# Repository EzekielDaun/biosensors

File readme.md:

# Biosensor

TODO: Description of the project itself.

## How to use Git

Before starting, be familiar with the [command line and shell](https://missing.csail.mit.edu/2020/course-shell/). (At least the `cd` command)

[Download and Installation Guide](https://git-scm.com/downloads)

### Resources

[Documentation](https://git-scm.com/doc)

[Cheat Sheet](https://training.github.com/downloads/github-git-cheat-sheet)

[Learn Git Branching](https://learngitbranching.js.org) (~1h) is an alternative to learning git branching interactively, and also a sandbox to play with.

### User

If you only want to use this repo but not change it:

- Clone the repository

  If you don't need any version-control feature from git, `Download ZIP` and you can omit the remaining sections of this readme.

  **Recommended:** `cd` to a place for the code (the `git clone` command will create a folder named `biosensors` under the working directory)

  ```git
  git clone https://github.com/SiEPIC/biosensors.git
  ```

- Get the latest update

  This will reset your local version to the remote version:

  ```git
  git reset --hard origin
  ```

- Switch to commit

  1. List commits

  ```git
  git log

      commit b4363207acb8847089aef8f59283cc06b60350ea (HEAD -> main, origin/main, origin/HEAD)
      Author: EzekielDaun <liuyifei0905@gmail.com>
      Date:   Fri Aug 26 16:57:51 2022 -0700

          📖 update RA-GUI readme

      commit 6c2b0750e4bcb03764c195b85f4f5f3b98b2843e
      Author: EzekielDaun <liuyifei0905@gmail.com>
      Date: Fri Aug 26 14:22:33 2022 -0700

          📖 add usage guide for pyOptomip

      commit a774aea0a90b7bd50cc8b93aa6908ee873252529
      Merge: e32ba9e 12f7248
      Author: Yifei Liu <34564223+EzekielDaun@users.noreply.github.com>
  ```

  2. No need to type the full commit hash

  ```git
  git reset b436320
  ```

- Switch to branch
  ```git
  git checkout my_branch
  ```

### Developer

It's highly recommended for developers to be familiar with all topics in [Git Branching](https://learngitbranching.js.org), especially the `remote` section.

A typical git workflow is like [this](https://git-scm.com/about/branching-and-merging) or as follows:

```mermaid
    gitGraph
       commit
       branch develop
       checkout develop
       commit
       checkout main
       merge develop
       checkout develop
       branch topic
       commit
       checkout develop
       commit
       merge topic
       commit
       checkout main
       merge develop
```

A more advanced version for large projects:[^1]

[^1]: At the time of this figure, the default branch naming convention is "master". Now, "main" is preferred. [More](https://github.com/github/renaming)

For our project (a few developers with less frequent commits), a single main branch with feature/hotfix branches is enough.

A proposed workflow is:

1. check out a new branch from `main` with a proper name
2. commit your changes and push that branch to remote
3. create a Pull Request (PR) to merge your changes into `main` and request other members to review
4. update, commit and push your following modifications to that PR branch
5. merge into the main branch
6. delete feature/hotfix branch.

```mermaid
    gitGraph
      checkout main
      commit
      branch feature1
      checkout feature1
      commit
      checkout main
      branch feature2
      checkout feature2
      commit
      checkout main
      merge feature1
      merge feature2
```

[GitHub-Flow](https://docs.github.com/en/get-started/quickstart/github-flow)

#### Merge Conflicts

When multiple members work on the same project, merge conflicts can be tricky. As of this writing, there has never been such a situation yet.

A few tips just in case it happens:

- When resolving merge conflicts, make sure to select the correct changes. Test the functionality after merge.
- Force push (`git push --force`) if you believe an overwrite is easier. And **BE CAREFUL**.
- Pull from origin frequently with the rebase option (`git pull --rebase`) to avoid/reveal potential conflicts in advance.

[More about force push and rebase](https://docs.gitlab.com/ee/topics/git/git_rebase.html)

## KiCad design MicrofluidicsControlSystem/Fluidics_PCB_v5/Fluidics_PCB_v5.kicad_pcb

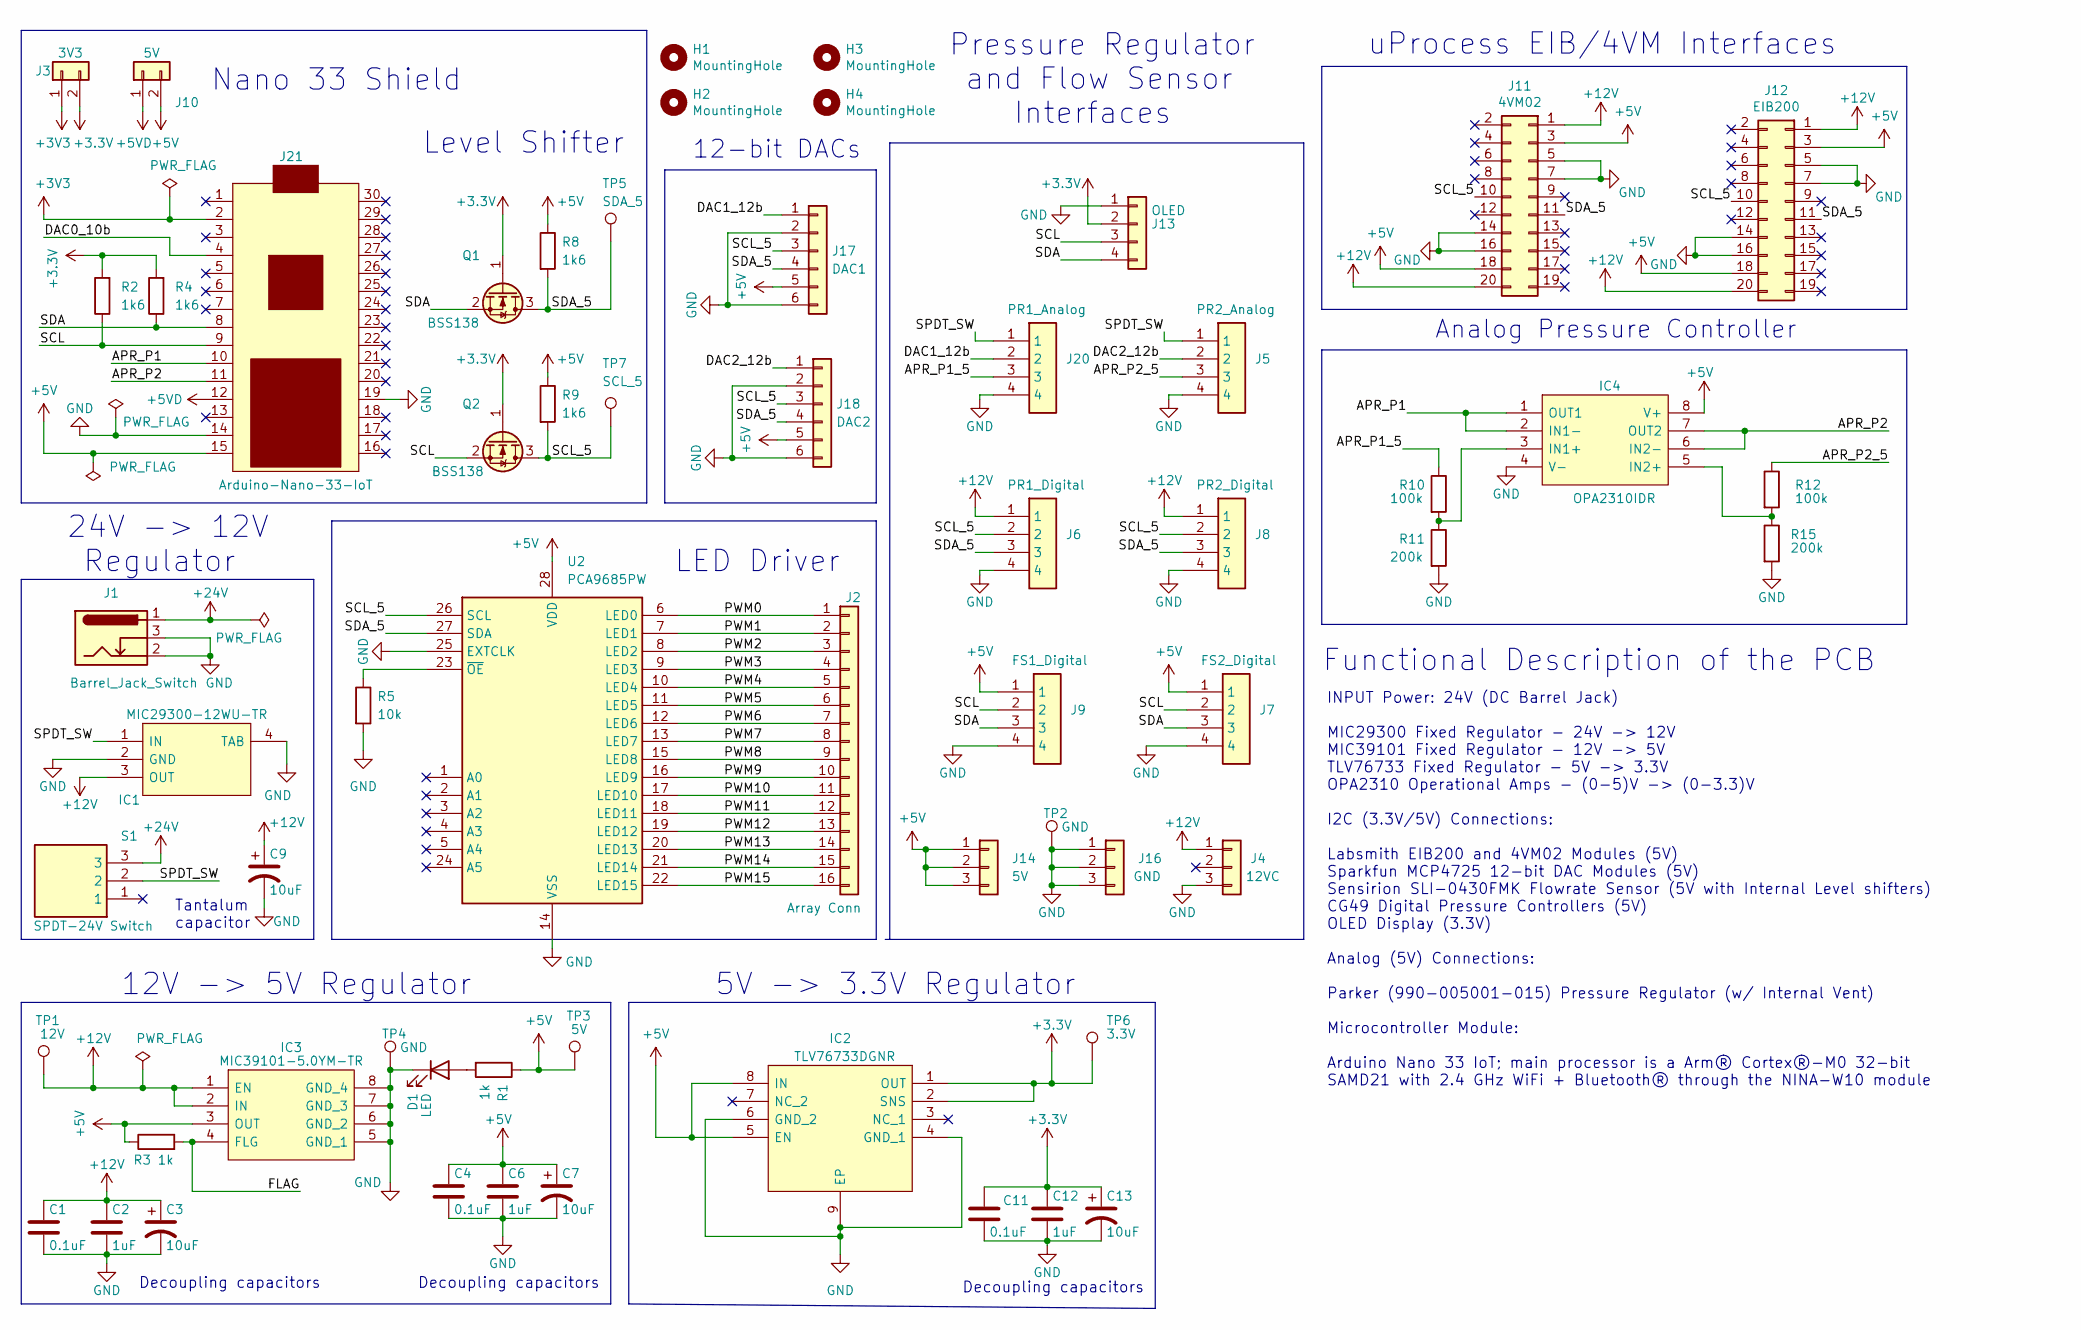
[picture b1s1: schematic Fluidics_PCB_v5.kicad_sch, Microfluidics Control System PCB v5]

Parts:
C1, C4, C11: 0.1uF; C_0603_1608Metric
C2, C6, C12: 1uF; C_0603_1608Metric
C3, C7, C13: 10uF; C_0805_2012Metric
C9: 10uF; CP_EIA-3528-12_Kemet-T
D1: LED; LED_0805_2012Metric
H1, H2, H3, H4: MountingHole; MountingHole_3.2mm_M3
IC1: MIC29300-12WU-TR; MIC2930012WUTR; Mouser Part Number 998-MIC29300-12WUTR
IC2: TLV76733DGNR; SOP65P490X110-9N; Manufacturer_Part_Number TLV76733DGNR; Mouser Part Number 595-TLV76733DGNR
IC3: MIC39101-5.0YM-TR; SOIC127P599X173-8N; Manufacturer_Part_Number MIC39101-5.0YM-TR; Mouser Part Number 998-MIC39101-5.0YMTR
IC4: OPA2310IDR; SOIC127P600X175-8N; Mouser Part Number 595-OPA2310IDR
J1: Barrel_Jack_Switch; BarrelJack_CLIFF_FC681465S_SMT_Horizontal
J2: Array Conn; PinSocket_2x08_P2.54mm_Vertical_SMD
J3: 3V3; PinHeader_1x02_P2.54mm_Vertical
J4: 12VC; PinSocket_1x03_P2.54mm_Vertical
J5: PR2_Analog; 110990030; Mouser Part Number 713-110990030
J6: PR1_Digital; 110990030; Mouser Part Number 713-110990030
J7: FS2_Digital; 110990030; Mouser Part Number 713-110990030
J8: PR2_Digital; 110990030; Mouser Part Number 713-110990030
J9: FS1_Digital; 110990030; Mouser Part Number 713-110990030
J10: 5V; PinHeader_1x02_P2.54mm_Vertical
J11: 4VM02
J12: EIB200
J13: OLED; PinSocket_1x04_P2.54mm_Vertical
J14: 5V; PinSocket_1x03_P2.54mm_Vertical
J16: GND; PinSocket_1x03_P2.54mm_Vertical
J17: DAC1; PinSocket_1x06_P2.54mm_Vertical
J18: DAC2; PinSocket_1x06_P2.54mm_Vertical
J20: PR1_Analog; 110990030; Mouser Part Number 713-110990030
J21: Arduino-Nano-33-IoT; NANO_33_Footprint_SMD_Castell
Q1, Q2: BSS138; SOT-23
R1, R3: 1k; R_0603_1608Metric
R2, R4, R8, R9: 1k6; R_0603_1608Metric
R5: 10k; R_0603_1608Metric
R10, R12: 100k; R_0603_1608Metric
R11, R15: 200k; R_0603_1608Metric
S1: SPDT-24V Switch; 8SS1012Z; Manufacturer_Part_Number 8SS1012-Z
TP1: 12V; TestPoint_THTPad_D2.0mm_Drill1.0mm
TP2, TP4: GND; TestPoint_THTPad_D2.0mm_Drill1.0mm
TP3: 5V; TestPoint_THTPad_D2.0mm_Drill1.0mm
TP5: SDA_5; TestPoint_THTPad_D2.0mm_Drill1.0mm
TP6: 3.3V; TestPoint_THTPad_D2.0mm_Drill1.0mm
TP7: SCL_5; TestPoint_THTPad_D2.0mm_Drill1.0mm
U2: PCA9685PW; TSSOP-28_4.4x9.7mm_P0.65mm

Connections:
+3.3V: C11.1, C12.1, C13.1, IC2.1 (OUT), IC2.2 (SNS), J3.2, J13.2, Q1.1 (G), Q2.1 (G), R2.2, R4.2, TP6.1
+3V3: J3.1, J21.2
+5V: C4.1, C6.1, C7.1, IC2.5 (EN), IC2.8 (IN), IC3.3 (OUT), IC4.8 (V+), J7.1, J9.1, J10.2, J11.3, J11.18, J12.3, J12.18, J14.1, J14.2, J14.3, J17.5, J18.5, J21.15, R1.1, R3.1, R8.1, R9.1, TP3.1, U2.28 (VDD)
+5VD: J10.1, J21.12
+12V: C1.1, C2.1, C3.1, C9.1, IC1.3 (OUT), IC3.1 (EN), IC3.2 (IN), J4.1, J6.1, J8.1, J11.1, J11.20, J12.1, J12.20, TP1.1
+24V: J1.1, S1.3
/APR_P1: IC4.1 (OUT1), IC4.2 (IN1-), J21.10
/APR_P1_5: J20.3, R10.1
/APR_P2: IC4.6 (IN2-), IC4.7 (OUT2), J21.11
/APR_P2_5: J5.3, R12.1
/DAC0_10b: J21.4
/DAC1_12b: J17.1, J20.2
/DAC2_12b: J5.2, J18.1
/FLAG: IC3.4 (FLG), R3.2
/PWM0: J2.1, U2.6 (LED0)
/PWM1: J2.2, U2.7 (LED1)
/PWM2: J2.3, U2.8 (LED2)
/PWM3: J2.4, U2.9 (LED3)
/PWM4: J2.5, U2.10 (LED4)
/PWM5: J2.6, U2.11 (LED5)
/PWM6: J2.7, U2.12 (LED6)
/PWM7: J2.8, U2.13 (LED7)
/PWM8: J2.9, U2.15 (LED8)
/PWM9: J2.10, U2.16 (LED9)
/PWM10: J2.11, U2.17 (LED10)
/PWM11: J2.12, U2.18 (LED11)
/PWM12: J2.13, U2.19 (LED12)
/PWM13: J2.14, U2.20 (LED13)
/PWM14: J2.15, U2.21 (LED14)
/PWM15: J2.16, U2.22 (LED15)
/SCL: J7.2, J9.2, J13.3, J21.9, Q2.2 (S), R2.1
/SCL_5: J6.2, J8.2, J11.10, J12.10, J17.3, J18.3, Q2.3 (D), R9.2, TP7.1, U2.26 (SCL)
/SDA: J7.3, J9.3, J13.4, J21.8, Q1.2 (S), R4.1
/SDA_5: J6.3, J8.3, J11.11, J12.11, J17.4, J18.4, Q1.3 (D), R8.2, TP5.1, U2.27 (SDA)
/SPDT_SW: IC1.1 (IN), J5.1, J20.1, S1.2
GND: C1.2, C2.2, C3.2, C4.2, C6.2, C7.2, C9.2, C11.2, C12.2, C13.2, D1.1 (K), IC1.2 (GND), IC1.4 (TAB), IC2.4 (GND_1), IC2.6 (GND_2), IC2.9 (EP), IC3.5 (GND_1), IC3.6 (GND_2), IC3.7 (GND_3), IC3.8 (GND_4), IC4.4 (V-), J1.2, J1.3, J4.3, J5.4, J6.4, J7.4, J8.4, J9.4, J11.5, J11.7, J11.14, J11.16, J12.5, J12.7, J12.14, J12.16, J13.1, J16.1, J16.2, J16.3, J17.2, J17.6, J18.2, J18.6, J20.4, J21.14, J21.19, R5.2, R11.2, R15.2, TP2.1, TP4.1, U2.14 (VSS), U2.25 (EXTCLK); also elsewhere on the board
unnamed: D1.2 (A), R1.2
unnamed: IC4.3 (IN1+), R10.2, R11.1
unnamed: IC4.5 (IN2+), R12.2, R15.1
unnamed: R5.1, U2.23 (~OE)

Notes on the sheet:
Pressure Regulator and Flow Sensor Interfaces
INPUT Power: 24V (DC Barrel Jack) MIC29300 Fixed Regulator - 24V -> 12V MIC39101 Fixed Regulator - 12V -> 5V TLV76733 Fixed Regulator - 5V -> 3.3V OPA2310 Operational Amps - (0-5)V -> (0-3.3)V I2C (3.3V/5V) Connections: Labsmith EIB200 and 4VM02 Modules (5V) Sparkfun MCP4725 12-bit DAC Modules (5V)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
uProcess EIB/4VM Interfaces
Decoupling capacitors
24V -> 12V Regulator
Analog Pressure Controller
Functional Description of the PCB
Tantalum capacitor
Level Shifter
Nano 33 Shield
12-bit DACs
5V -> 3.3V Regulator
LED Driver
12V -> 5V Regulator

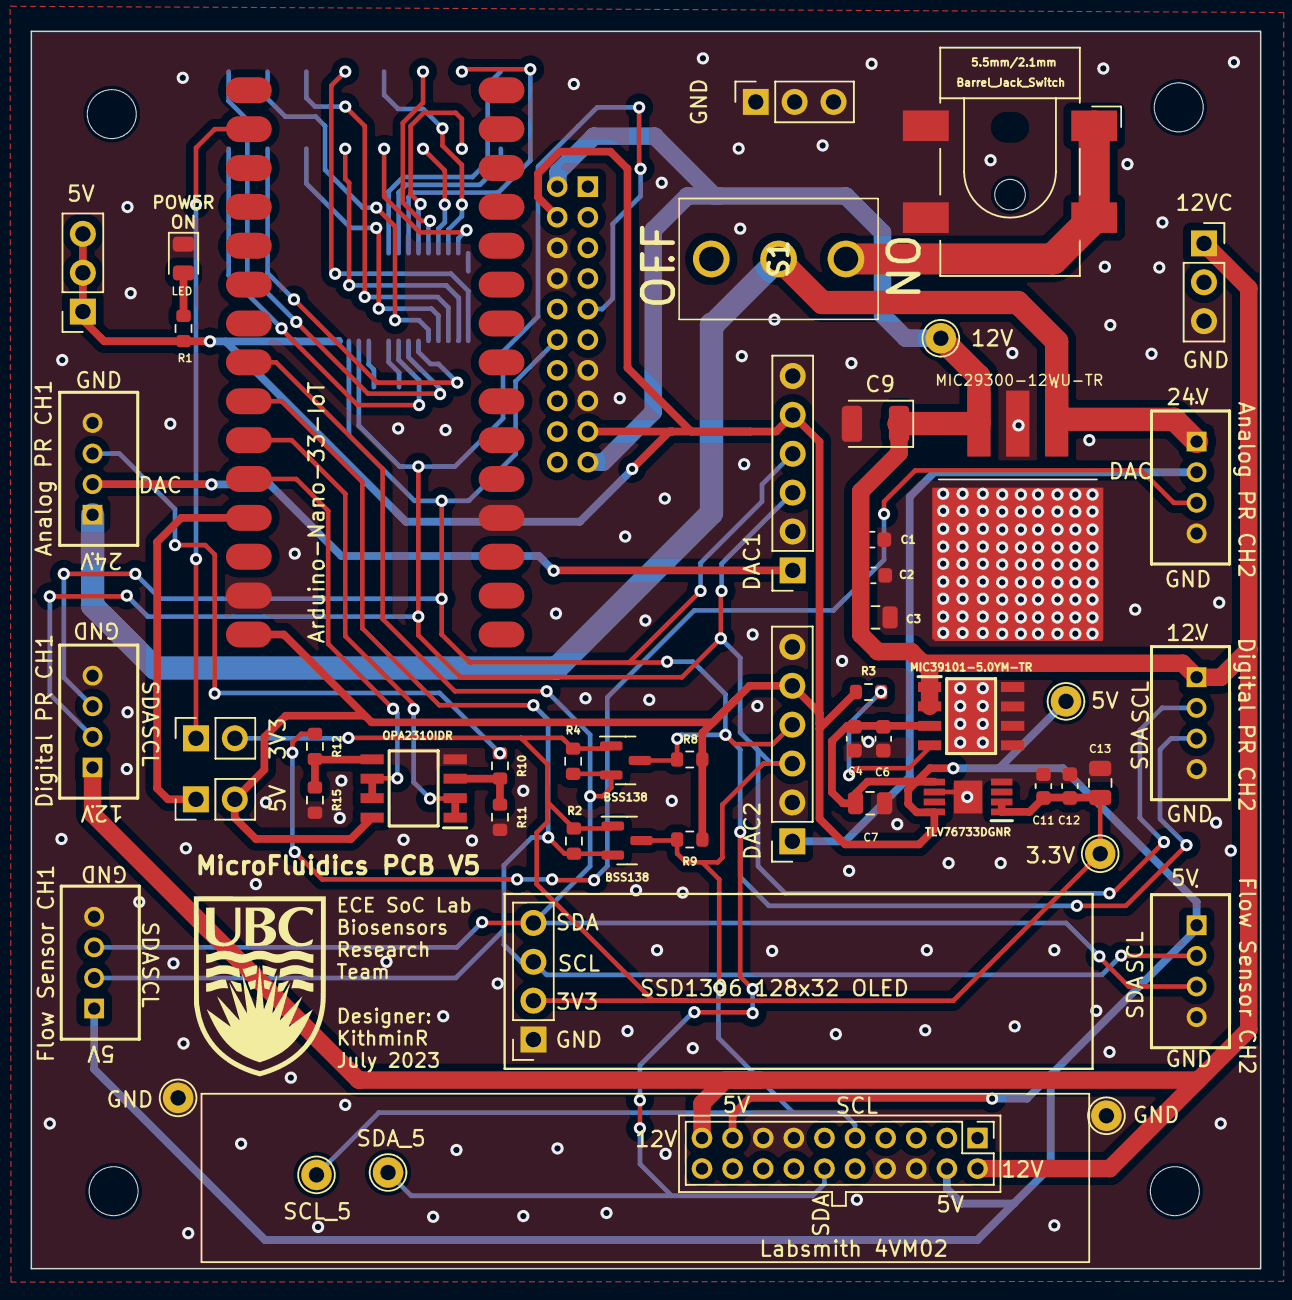
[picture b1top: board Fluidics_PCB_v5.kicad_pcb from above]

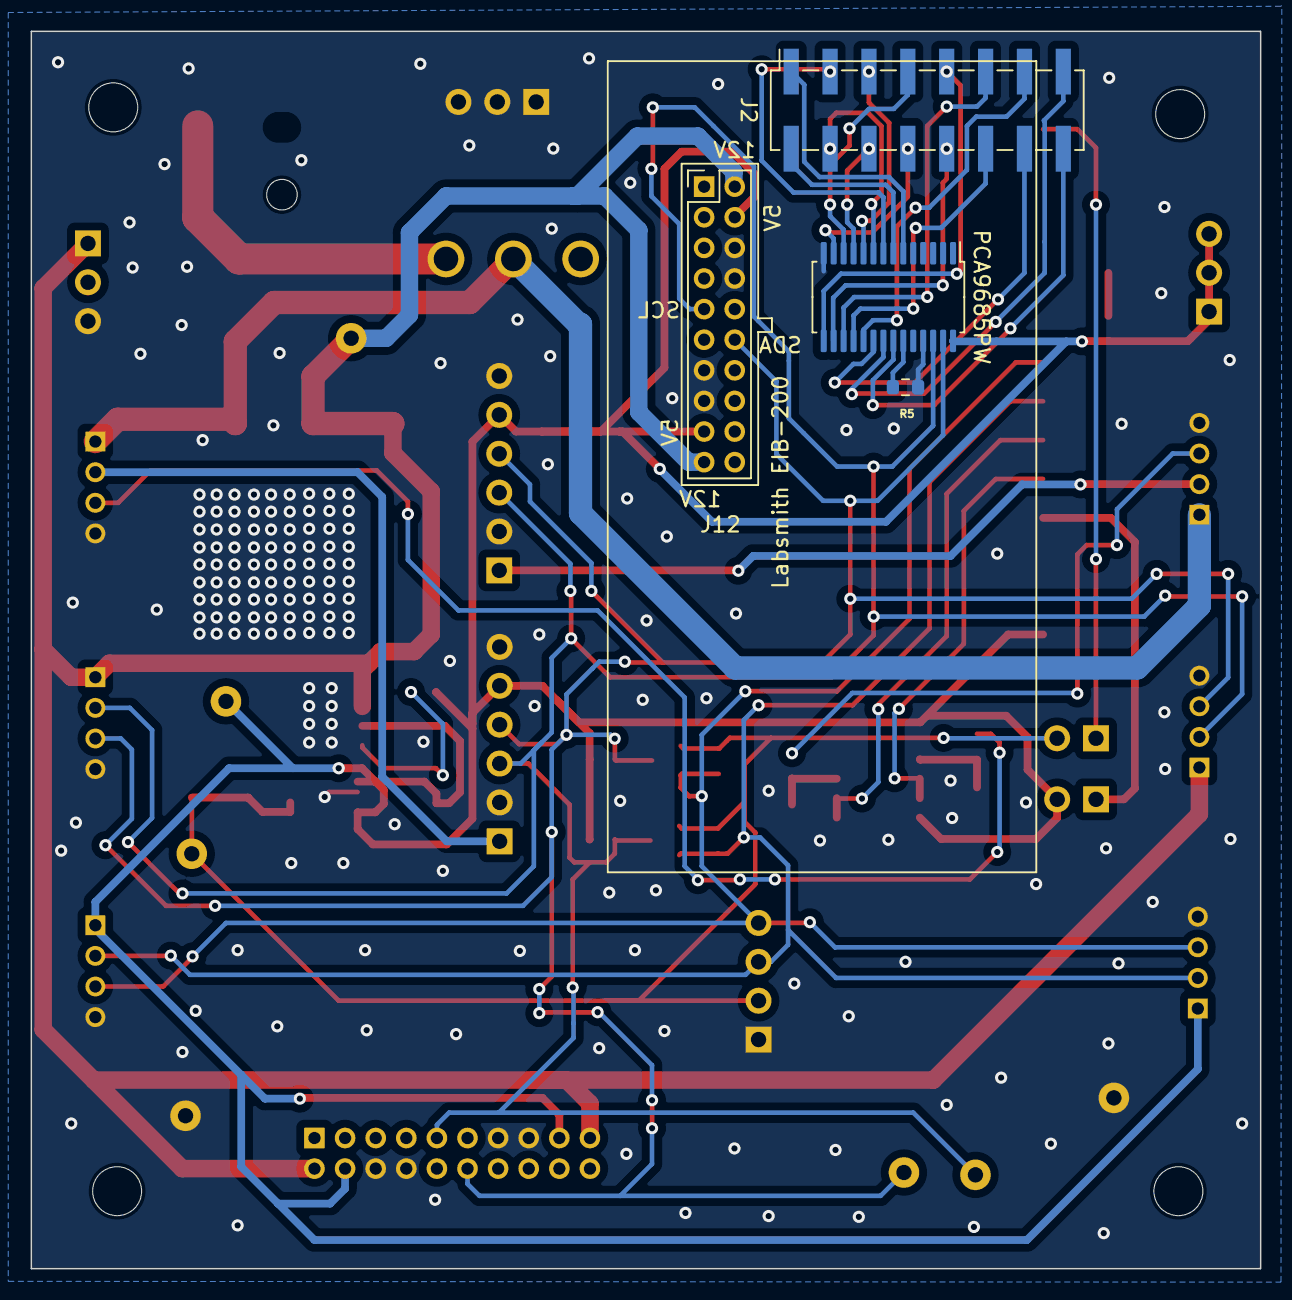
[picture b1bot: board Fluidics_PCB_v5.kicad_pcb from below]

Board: 2 copper layers, 80.3 x 80.8 mm, 62 parts (6 on the bottom side), 39 nets.

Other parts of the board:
GND: SolderWirePad_1x01_SMD_5x10mm
GND#2: SolderWirePad_1x01_SMD_5x10mm

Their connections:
GND: GND.1, GND#2.1; also elsewhere on the board

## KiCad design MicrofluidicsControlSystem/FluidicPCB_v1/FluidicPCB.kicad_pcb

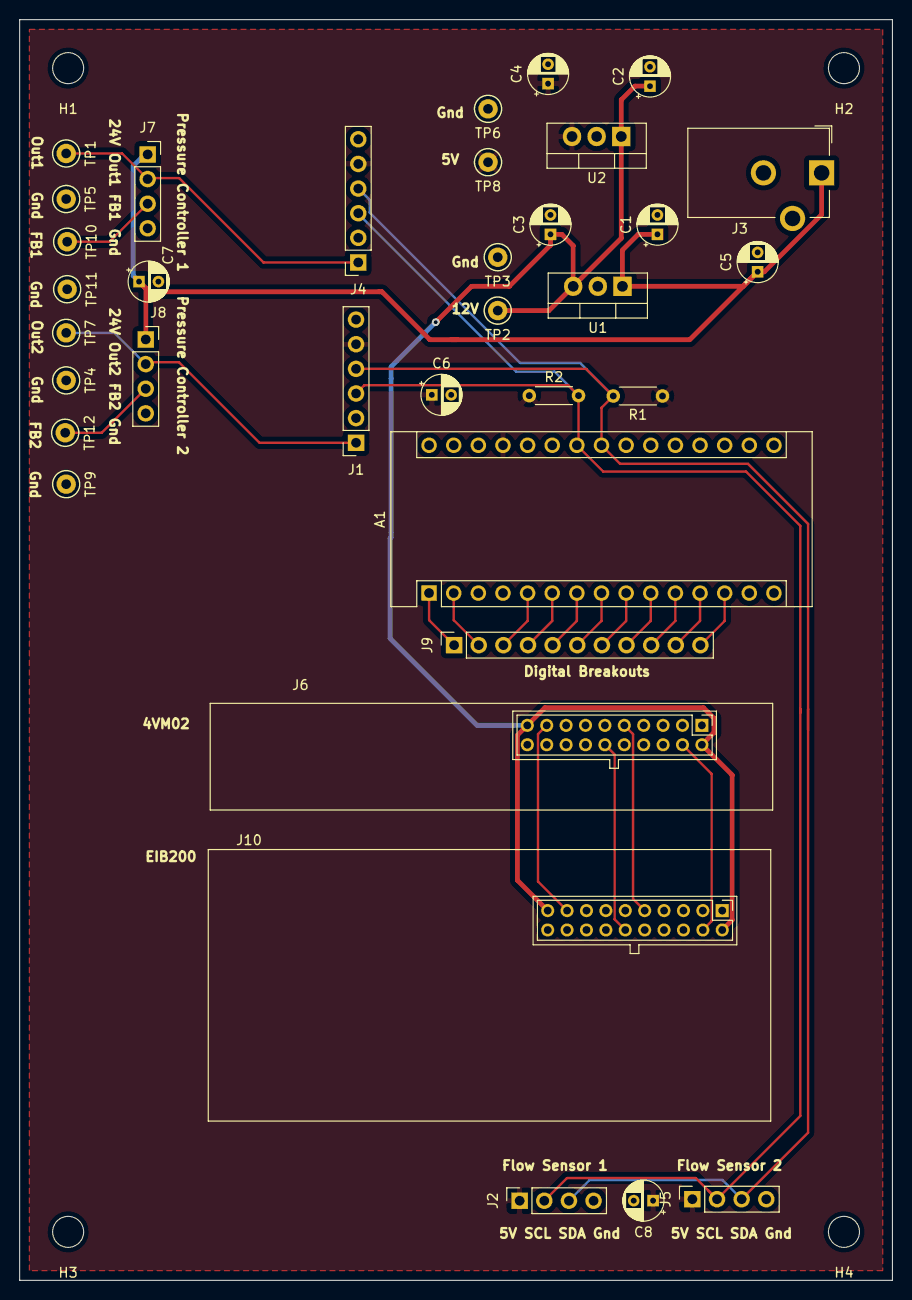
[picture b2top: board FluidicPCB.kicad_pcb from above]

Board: 2 copper layers, 90.0 x 130.0 mm, 39 parts (0 on the bottom side), 25 nets.

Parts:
A1: Arduino_Nano_Every; Arduino_Nano
C1, C3, C6, C7, C8: 0.1u; CP_Radial_D4.0mm_P2.00mm
C2, C4: 0.33u; CP_Radial_D4.0mm_P2.00mm
C5: 4.7u; CP_Radial_D4.0mm_P2.00mm
H1, H2, H3, H4: MountingHole; MountingHole_3.2mm_M3
J1: DAC1; PinSocket_1x06_P2.54mm_Vertical
J2: Flow1; PinSocket_1x04_P2.54mm_Vertical
J3: Barrel_Jack_Switch; BarrelJack_CUI_PJ-102AH_Horizontal
J4: DAC2; PinSocket_1x06_P2.54mm_Vertical
J5: Flow2; PinSocket_1x04_P2.54mm_Vertical
J6: 4VM02
J7: Pressure1; PinSocket_1x04_P2.54mm_Vertical
J8: Pressure2; PinSocket_1x04_P2.54mm_Vertical
J9: breakout; PinSocket_1x11_P2.54mm_Vertical
J10: EIB200
R1, R2: 4.7k; R_Axial_DIN0204_L3.6mm_D1.6mm_P5.08mm_Horizontal
TP1, TP2, TP3, TP4, TP5, TP6, TP7, TP8, TP9, TP10, TP11, TP12: TestPoint; TestPoint_Keystone_5000-5004_Miniature
U1: L7812; TO-220-3_Vertical
U2: L7805; TO-220-3_Vertical

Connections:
/5V: A1.27 (+5V), C4.1, C6.1, C8.1, J1.5, J2.1, J4.5, J5.1, R1.1, R2.1, TP8.1, U2.3 (OUT)
/5V_LS1: J6.3, J10.3
/5V_LS2: J6.18, J10.18
/12V: C2.1, C3.1, J6.1, J6.20, J10.1, J10.20, TP2.1, U1.3 (OUT), U2.1 (IN)
/24V: C1.1, C5.1, C7.1, J3.1, J7.1, J8.1, U1.1 (IN)
/MONITOR1: J7.3, TP10.1
/MONITOR2: J8.3, TP12.1
/OUT1: J4.1, J7.2, TP1.1
/OUT2: J1.1, J8.2, TP7.1
/SCL: A1.24 (SCL/A5), J1.3, J2.2, J4.3, J5.2, R2.2
/SCL_2: J6.10, J10.10
/SDA: A1.23 (SDA/A4), J1.4, J2.3, J4.4, J5.3, R1.2
/SDA_2: J6.11, J10.11
GND: A1.4 (GND), A1.29 (GND), C1.2, C2.2, C3.2, C4.2, C5.2, C6.2, C7.2, C8.2, J1.2, J1.6, J2.4, J3.2, J4.2, J4.6, J5.4, J6.5, J6.7, J6.14, J6.16, J7.4, J8.4, J10.5, J10.7, J10.14, J10.16, TP3.1, TP4.1, TP5.1, TP6.1, TP9.1, TP11.1, U1.2 (GND), U2.2 (GND)
unnamed: A1.1 (TX1), J9.1
unnamed: A1.2 (RX1), J9.2
unnamed: A1.5 (D2), J9.3
unnamed: A1.6 (D3), J9.4
unnamed: A1.7 (D4), J9.5
unnamed: A1.8 (D5), J9.6
unnamed: A1.9 (D6), J9.7
unnamed: A1.10 (D7), J9.8
unnamed: A1.11 (D8), J9.9
unnamed: A1.12 (D9), J9.10
unnamed: A1.13 (D10), J9.11

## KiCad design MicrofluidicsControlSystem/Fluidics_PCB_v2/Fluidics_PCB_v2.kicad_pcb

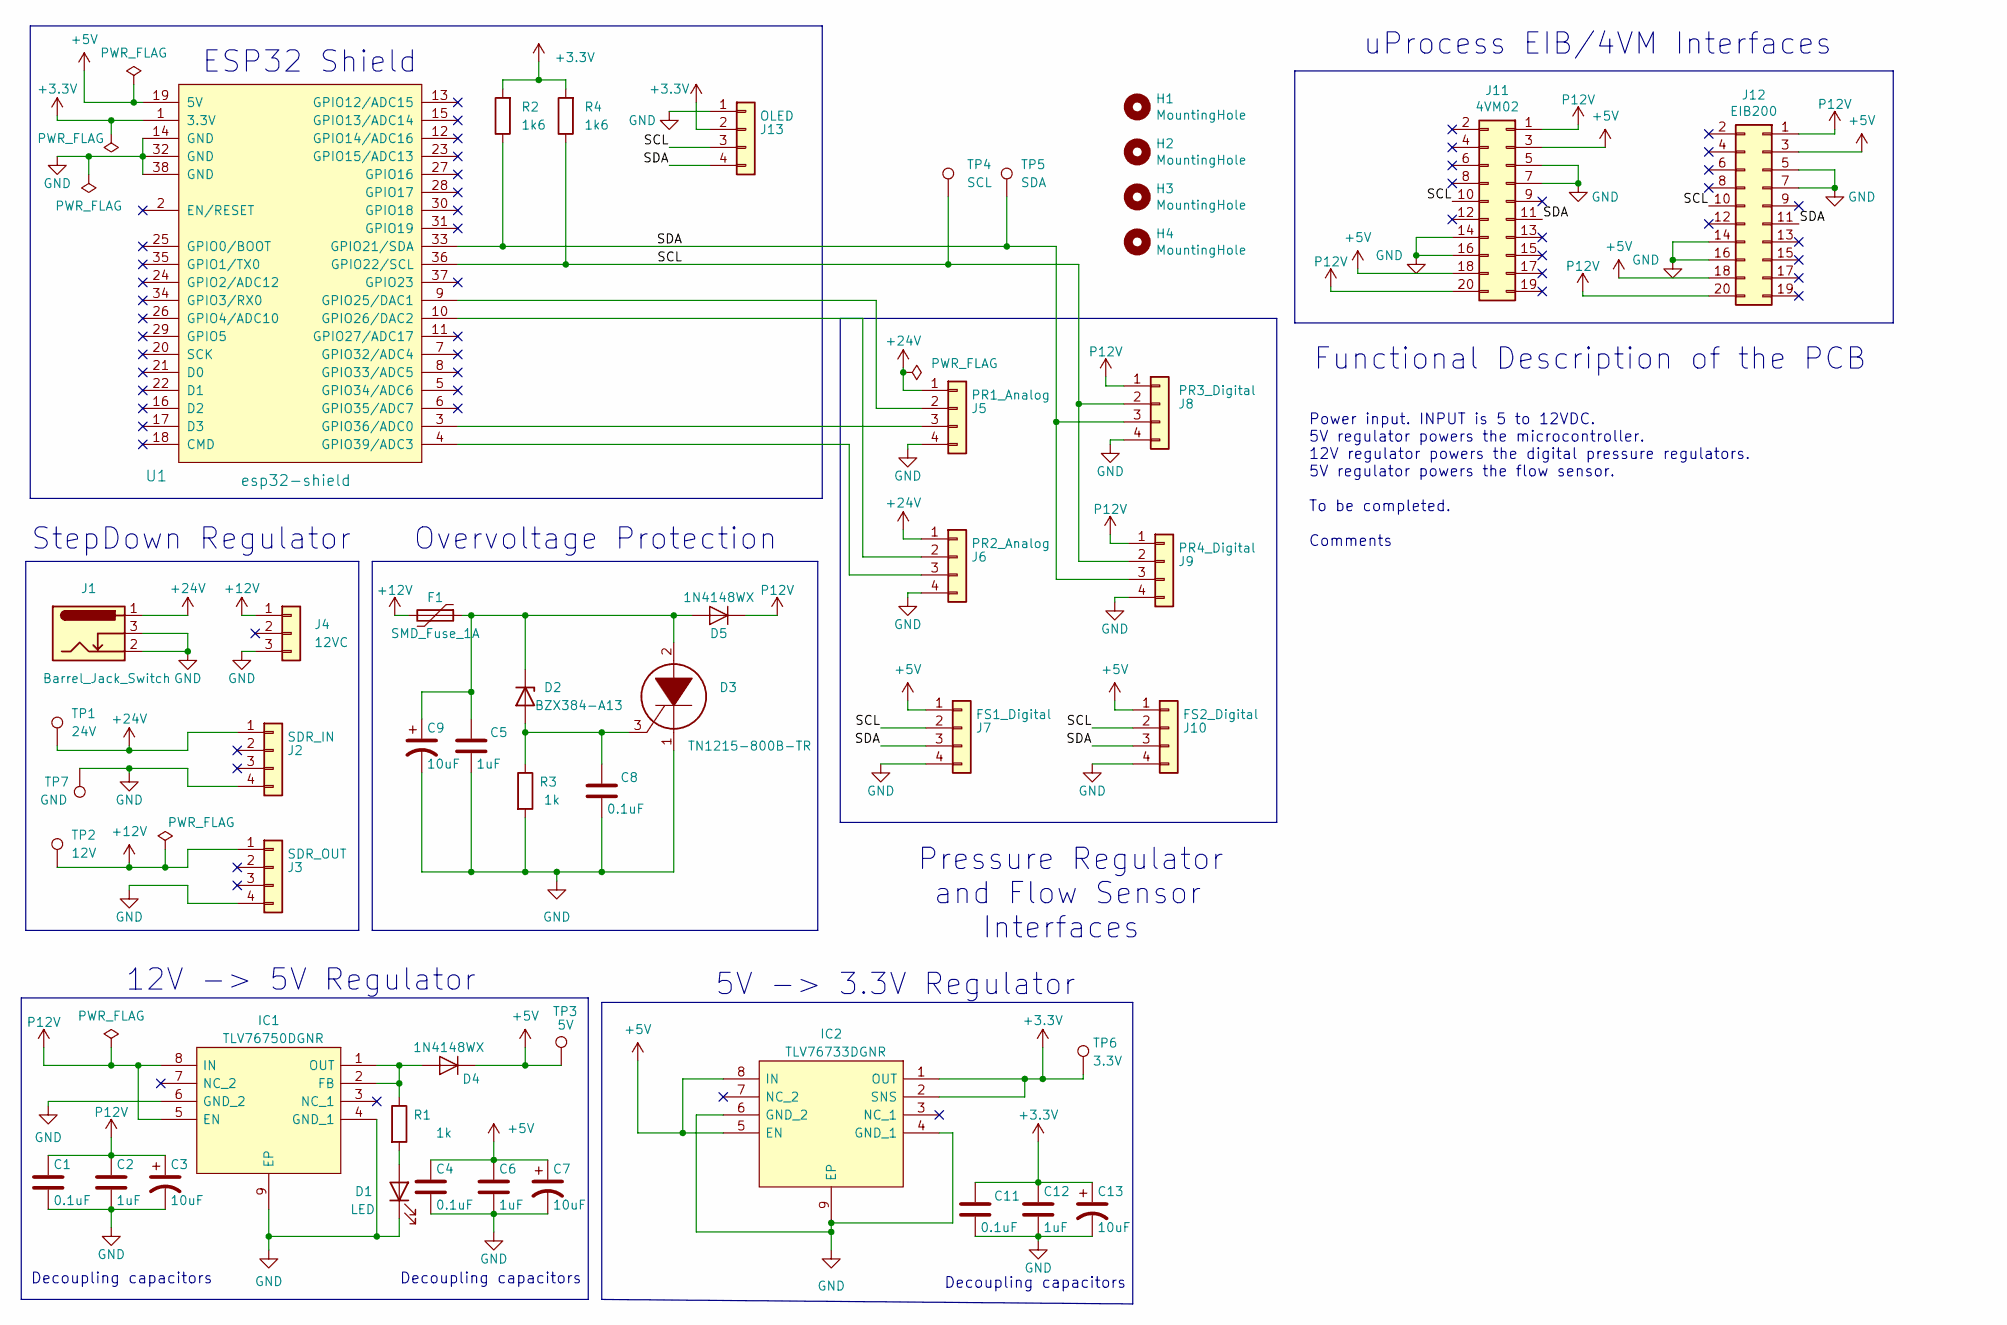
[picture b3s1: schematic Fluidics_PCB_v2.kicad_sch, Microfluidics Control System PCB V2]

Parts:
C1, C4, C8, C11: 0.1uF; C_0603_1608Metric
C2, C5, C6, C12: 1uF; C_0603_1608Metric
C3, C7, C9, C13: 10uF; C_0805_2012Metric
D1: LED; LED_0805_2012Metric
D2: BZX384-A13; SOD2512X115N
D3: TN1215-800B-TR; TN1215600BTR; Mouser Part Number 511-TN1215-600B-TR
D4, D5: 1N4148WX; SOD2512X115N
F1: SMD_Fuse_1A; FUSC1608X30N
H1, H2, H3, H4: MountingHole; MountingHole_3.2mm_M3
IC1: TLV76750DGNR; SOP65P490X110-9N; Manufacturer_Part_Number TLV76750DGNR; Mouser Part Number 595-TLV76750DGNR
IC2: TLV76733DGNR; SOP65P490X110-9N; Manufacturer_Part_Number TLV76733DGNR; Mouser Part Number 595-TLV76733DGNR
J1: Barrel_Jack_Switch; BarrelJack_CLIFF_FC681465S_SMT_Horizontal
J2: SDR_IN; PinSocket_1x04_P2.54mm_Vertical
J3: SDR_OUT; PinSocket_1x04_P2.54mm_Vertical
J4: 12VC; PinSocket_1x03_P2.54mm_Vertical
J5: PR1_Analog; 470531000
J6: PR2_Analog; 470531000
J7: FS1_Digital; 470531000
J8: PR3_Digital; 470531000
J9: PR4_Digital; 470531000
J10: FS2_Digital; 470531000
J11: 4VM02
J12: EIB200
J13: OLED; PinSocket_1x04_P2.54mm_Vertical
R1, R3: 1k; R_0603_1608Metric
R2, R4: 1k6; R_0603_1608Metric
TP1: 24V; TestPoint_THTPad_D2.0mm_Drill1.0mm
TP2: 12V; TestPoint_THTPad_D2.0mm_Drill1.0mm
TP3: 5V; TestPoint_THTPad_D2.0mm_Drill1.0mm
TP4: SCL; TestPoint_THTPad_D2.0mm_Drill1.0mm
TP5: SDA; TestPoint_THTPad_D2.0mm_Drill1.0mm
TP6: 3.3V; TestPoint_THTPad_D2.0mm_Drill1.0mm
TP7: GND; TestPoint_THTPad_D2.0mm_Drill1.0mm
U1: esp32-shield; ESP32_devkit

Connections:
+3.3V: C11.1, C12.1, C13.1, IC2.1 (OUT), IC2.2 (SNS), J13.2, R2.2, R4.2, TP6.1, U1.1 (3.3V)
+5V: C4.1, C6.1, C7.1, D4.1 (K), IC2.5 (EN), IC2.8 (IN), J7.1, J10.1, J11.3, J11.18, J12.3, J12.18, TP3.1, U1.19 (5V)
+12V: F1.2, J3.1, J4.1, TP2.1
+24V: J1.1, J2.1, J5.1, J6.1, TP1.1
/SCL: J7.2, J8.2, J9.2, J10.2, J11.10, J12.10, J13.3, R4.1, TP4.1, U1.36 (GPIO22/SCL)
/SDA: J7.3, J8.3, J9.3, J10.3, J11.11, J12.11, J13.4, R2.1, TP5.1, U1.33 (GPIO21/SDA)
GND: C1.2, C2.2, C3.2, C4.2, C5.2, C6.2, C7.2, C8.2, C9.2, C11.2, C12.2, C13.2, D1.1 (K), D3.1, IC1.4 (GND_1), IC1.6 (GND_2), IC1.9 (EP), IC2.4 (GND_1), IC2.6 (GND_2), IC2.9 (EP), J1.2, J1.3, J2.4, J3.4, J4.3, J5.4, J6.4, J7.4, J8.4, J9.4, J10.4, J11.5, J11.7, J11.14, J11.16, J12.5, J12.7, J12.14, J12.16, J13.1, R3.2, TP7.1, U1.14 (GND), U1.32 (GND), U1.38 (GND)
unnamed: C5.1, C9.1, D2.1 (K), D3.2, D5.2 (A), F1.1
unnamed: C8.1, D2.2 (A), D3.3, R3.1
unnamed: D1.2 (A), R1.2
unnamed: D4.2 (A), IC1.1 (OUT), IC1.2 (FB), R1.1
unnamed: J5.2, U1.9 (GPIO25/DAC1)
unnamed: J5.3, U1.3 (GPIO36/ADC0)
unnamed: J6.2, U1.10 (GPIO26/DAC2)
unnamed: J6.3, U1.4 (GPIO39/ADC3)
P12V: C1.1, C2.1, C3.1, D5.1 (K), IC1.5 (EN), IC1.8 (IN), J8.1, J9.1, J11.1, J11.20, J12.1, J12.20

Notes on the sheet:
Pressure Regulator and Flow Sensor Interfaces
Power input. INPUT is 5 to 12VDC. 5V regulator powers the microcontroller. 12V regulator powers the digital pressure regulators. 5V regulator powers the flow sensor. To be completed. Comments
uProcess EIB/4VM Interfaces
Decoupling capacitors
Functional Description of the PCB
Overvoltage Protection
ESP32 Shield
StepDown Regulator
5V -> 3.3V Regulator
12V -> 5V Regulator

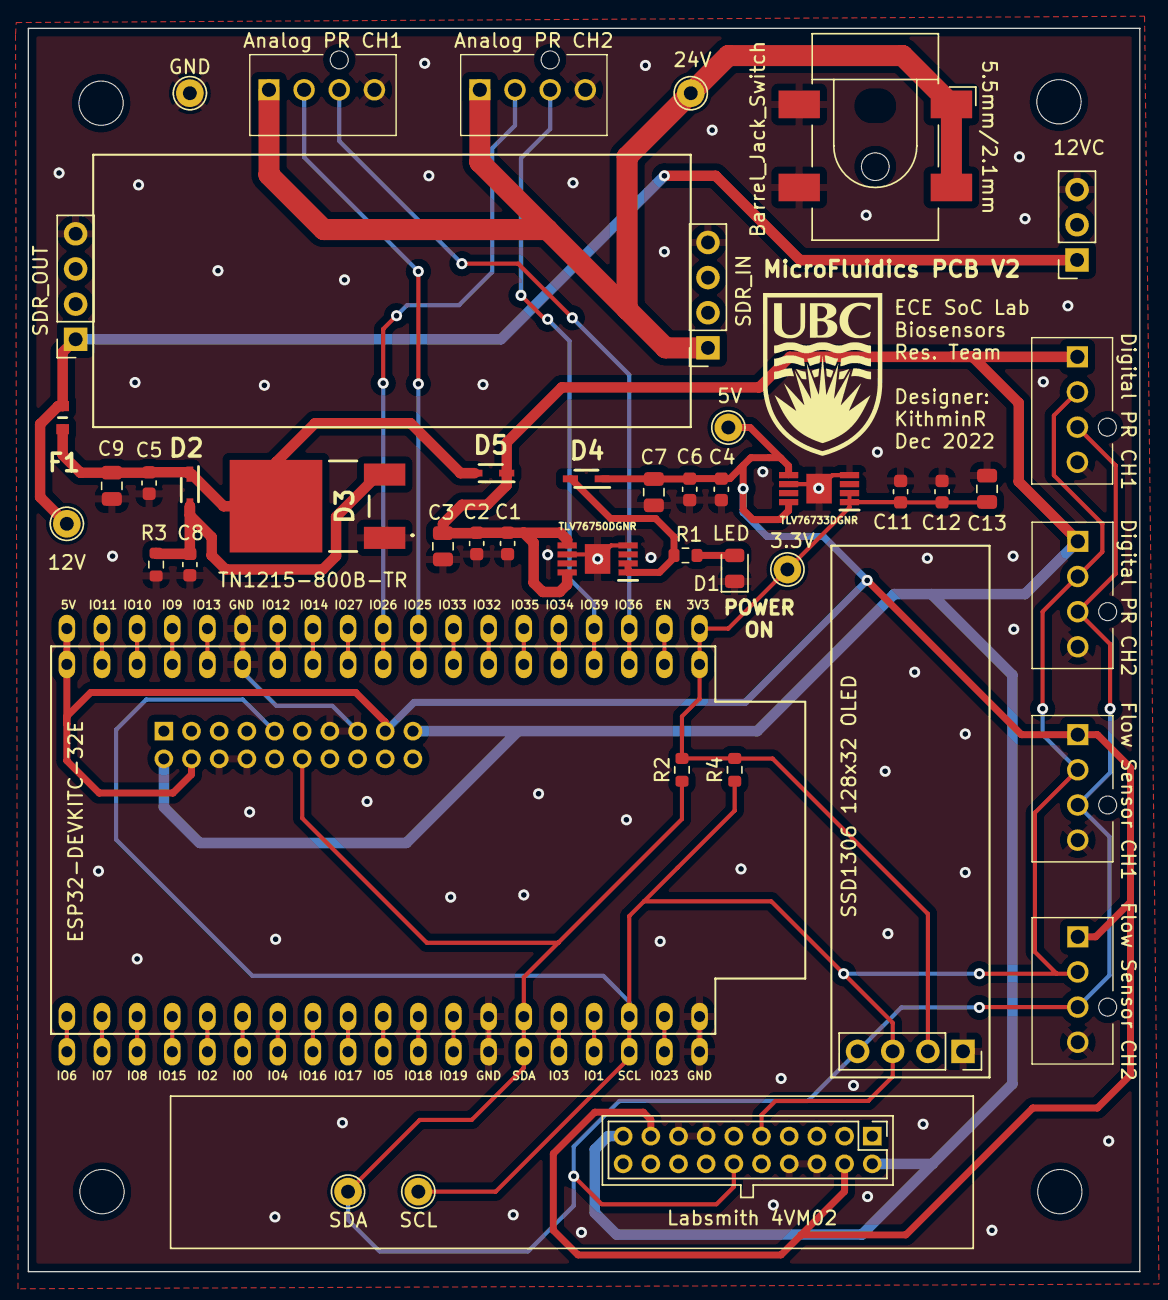
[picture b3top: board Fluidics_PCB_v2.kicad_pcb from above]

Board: 2 copper layers, 80.3 x 89.8 mm, 49 parts (1 on the bottom side), 16 nets.

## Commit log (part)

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2021-04-06 Original commit of the biosensor code as of March 2021
    This commit logs the state of the biosensor code, as shared with me by Vinny Randhawa March 30, 2021. My understanding is that the code was primarily authored by Michael Caverley and Eric Lyall (from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
2021-04-06 Create .gitignore
    Want to avoid committing .pyc files.
2021-04-06 Update RetrospectiveAnalysis.py to be more robust to large peak shifts
    Updated RetrospectiveAnalysis.py to reduce un-tracked ‘FSR hopping’ (switching the tracked peak due to (1) peak migration outside of the narrow sweep range or (2) fast shifts on the order of FSR/2 in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
2021-04-14 Updated so that the peak prominence threshold is not hard-coded, and individual channel figures are saved
    Modified RetrospectiveAnalysis.py and MultiLorentzianFit.py so that pkProm, the peak prominence threshold, is not hard-coded but rather passed as a parameter and consistent between the two scripts.
    Also updated the offset figure plot/save to plot the two channels together as well as separate figures.
2021-07-22 Update retrospective analysis script to make spectrogram plots
    Added functionality to the retrospective analysis script to make and save spectrogram plots (2D image with x-axis time, y-axis wavelength, colour representing the measured power) for debugging/visual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
2021-07-30 sensor update [WIP]
2021-07-31 Shuksan sensor update
2021-08-01 sensor chip, 5x5
2021-08-01 Shuksan sensor: fix
2021-08-01 Shuksan sensor: complete
2021-10-25 added GUI to interface with fluid delivery system
2021-11-23 Update Retrospective_Analysis_Script.py
    Added plotting spectrogram comparison, improved peak tracking robustness.
2021-11-24 8164A User Manual
2021-12-10 added to multichannel functions
2022-06-06 The script and files for the ANT troubleshooting scripted layout
2022-06-06 Removed
2022-06-08 retrospective gui with stand alone analysis script
2022-06-08 ✨ Integrate analysis figures into GUI
2022-06-15 ✨ click analyze now can process 6 detectors
2022-06-17 📖 update basic setup instruction
2022-06-23 🙈 update gitignore and requirements.txt
2022-07-11 Update FluigentLogFileAnalysis.m
    Matlab script to plot Fluigent Log Files.
2022-07-18 🔖 RA-GUI-Alpha-1
2022-07-21 🐛 Bug Fix: * add t_array to saved results * fix result naming to be compatible with old postprocessing script
2022-07-25 🎨 isort imports
2022-08-01 Adding alpha version of quantify_resonator_data.m
    Adding a new script to quantify resonator performance (ER, Q, FSR, FWHM, finesse) from a batch of .mat files.
2022-08-07 Update quantify_resonator_data.m with first implementation of fit to linearized data
    Added preliminary working version of the option to fit the Lorentzian to either the linearized or the dB-scale data. If linearized data, the FWHM is calculated at the midpoint of the fit (at the valu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
2022-08-07 Update quantify_resonator_data.m
    Fixed typo in figure 3 title.
2022-08-11 🐛 Fix infinite loop bug The script will not get stuck when there is only one peak in a sweep.
2022-08-11 Updated quantify_resonator_data to filter out very low intensity datasets
    Updated quantify_resonator_data to filter out very low intensity datasets so that it does not attempt to run analysis on noise
    Added washer designs for the ANT troubleshooting fluidics
2022-08-13 Update quantify_resonator_data.m with peak region R^2 and residual plots
    Update quantify_resonator_data.m:
    - Added the capability to export an R^2 value calculated only over the peak regions (excluding the baseline)
    - Added subplots on the fit plots to also plot the residuals
    - Added the analyzed wavelength range to the saved data
2022-08-15 Update quantify_resonator_data.m
    Fixed typo in comment about the linearizeFit flag
2022-08-20 🐛 Fix manual peak traces adjustment bug
2022-08-23 🚑 auto initialize plotname
2022-08-25 📖 use `python` instead of `pythonw`
2022-08-26 🔧 Config logging level to INFO
2022-08-26 📖 update RA-GUI readme
2022-08-29 📖 add instructions in using git
2022-08-31 📖 refine git usage guide
2022-09-03 ✨ save config file to folder automatically
2022-10-24 Create iLoD_benchmarking_plot
2022-11-08 Plot reservoir concentrations, flow rates, pressure
2022-11-28 Add files via upload
    Trapezoidal SWG:
    - Auto-aligned input and boolean-controlled add/drop port.
    - Adjustable fishbone position (centered or on edge)
    - Trapezoidal gratings
2022-12-01 Add files via upload
    Trapezoidal and Rectangular SWG Microrings:
    - Double bus (or single bus - pcell param) microring
    - Trapezoidal Grating (controllable taper, fishbone width, grating lengths)
    - Bus/Grating auto-alignment for different duty cycles
    - Fixed bugs with pins
    - Cleaned up the code significantly. Removed many portions which were cluttering/confusing the code - since it was derived from a different pymacro
2022-12-08 Updated the SRS_LDC501 with pyvisa
2022-12-16 Create file1
2022-12-23 Allow consecutive file number not starting from 1
2022-12-26 Allow non-consecutive file numbers Allow timeSteps.csv having more entries than needed.
2023-01-09 RA: Update type hint
2023-01-09 RA: fix exception channel number
2023-01-09 RA: catch fitting error, allow restart tracking
2023-01-10 RA: add installation and run powershell script
2023-01-10 RA: update readme for install and run scripts
2023-01-11 RA: bug fix on saving results
2023-01-17 RA: peak-tracking bug fix fix if only one peak found and the shape not match
2023-01-18 RA: add tooltips
2023-01-19 Add files via upload
    A module to assist in post-processing of optical data (from the retrospective analysis) and fluidic data (from Fluigent log files) in Python.
2023-01-20 RA: add filter, peak find option to file plotter
2023-01-20 RA: adjustable cosine similarity weight (no UI)
2023-01-20 RA: enhance file plotter peak find functionality
2023-01-24 RA: better display naive find_peaks
2023-01-24 RA: bugfix when only one peak in sweep after fit
2023-01-27 RA: add more descriptions
2023-01-30 RA: minor improvements
2023-02-01 RA: refactor multiprocessing code
2023-02-02 RA: select path bug fix
2023-02-08 RA: slice plotting bugfix
2023-02-20 RA: add step function to peak tracking
2023-02-24 RA: rewrite peak finding and fitting function
2023-02-24 RA: adjust fitting y0 bound. add more debug info
2023-03-02 RA: refactor for fsr, er, q
2023-03-07 RA: correct Q calculation formula
2023-03-07 Update calculate_shifts_slopes_interactive.m to address plotting bug
    Updated calculate_shifts_slopes_interactive.m with a few changes:
    -Fixed bug where the dotted lines indicating click position and averaged region were not visible on the plot
    -Made the script compatible with both PC and Mac without manually changing slash direction
    -Made it no longer necessary to update the config file path for each dataset to be analyzed (use uiopen to ask the user to navigate to the directory, rather than having it hard-coded)
2023-03-10 RA: ignore -100dBm values, remove fitting baseline check, improve Q algorithm
2023-03-14 RA: Q related changes
    * adjust linear curve fitting parameters
    * display Q result in .4g
    * other bug fixes
2023-03-21 pyOptomip: update wxPython version
2023-03-21 RA: fix typing, remove unused code
2023-03-24 RA: update readme * typo fixes * add descriptions for .mat outputs
2023-03-27 Created directory for BiosensorFlowsensor
2023-03-31 RA: update readme for first sweep no peak issue
2023-03-31 RA: raise runtime error with possible reason
2023-04-04 RA: fsr-er-q output as .mat with updated UI
2023-04-04 RA: rename output variable names
2023-04-12 RA: readme typo
2023-04-27 RA: revise comments, remove unused code
2023-05-05 refactor🎨: RA: core lib structure. Sort imports
2023-05-09 Adding N77 data stream in scripts!
2023-05-09 refactor🎨: pyOptomip: remove unused code
2023-05-11 pyOptomip: active acquisition code compatibility * pyvisa must be 1.9.0 for N774xA.py * remove all python2 reload()
2023-05-23 fix N77 data acquisition timestamp issue
2023-06-07 Adding Fluidics_PCB_v4
2023-06-14 RA: loose restrictions related to -100dBm data
2023-06-22 Slight updates to postprocessing folder organization
    Shifted location of Colormaps folder to follow script organization.
2023-06-27 RA: RA-Converter for active data
2023-06-27 RA: support click-and-drag adjustment
2023-06-27 R2 threshold and -100 dBm threshold setting
2023-06-27 RA: minimum Python version >= 3.11
2023-06-27 RA: update peak tracking color palette
2023-06-27 firmware_v1 folder created
2023-06-28 RA: converter add equation display
2023-07-07 RA: converter supports triangle and down ramp
2023-07-10 RA: add panel display manager on Window menu
2023-07-11 RA: refactor output file saving and naming
2023-07-17 RA: base RA save all spectrograms button
2023-07-19 RA: feat✨: add shortcut to start page
2023-07-20 feat✨: RA: watcher mode can plot single spectrum
2023-07-20 RA: style💄: fix dark mode issue
2023-07-22 RA: feat✨: redirect tqdm progress bar to qt
2023-07-25 style💄: RA: Rearrange startup window
2023-07-25 RA: style💄: external link to RegEx generator
2023-07-25 RA: style💄: make active-converter a normal window
2023-07-28 RA: style💄: add block diagram and update equations display
2023-07-31 LabSmith 4VM02 v1 reverse engineering schematics
2023-08-02 RA: perf👌: improve watch mode performance
2023-08-04 RA: style💄: allow more digits in step
2023-08-09 RA: feat✨: add progress bar to active-converter
2023-08-09 RA: fix🐛: tune curvefit threshold for active data
2023-08-09 RA: style💄: active-converter rename LTI plot legend
2023-08-09 RA: style💄: active rename output filename
2023-08-10 MultiSweepGUI V.1
2023-08-10 RA: fix🐛: group_peaks correctly handle 0d array
2023-08-11 RA: style💄: converter: fix spectrogram title
2023-08-12 RA: refactor🎨: refactor passive core code
2023-08-14 RA: refactor🎨: continue refactor passive code. timestamp bugfix
2023-08-14 RA: config🔧: fix import path
2023-08-15 RA: format🥚: refine type hint in active window
2023-08-15 RA: style💄: redesign active converter GUI layout
2023-08-16 RA: refactor🎨: extract workers to lib
2023-08-21 RA: fix🐛: peak tracking fix the first nan value
2023-08-22 RA: fix🐛: fix timestamp range display issue
2023-08-23 RA: style💄: active converter fix layout issue
2023-08-23 RA: docs📝: developer guide mdbook outline
2023-08-23 RA: fix🐛: converter ramp down bug fix
2023-08-28 RA: docs📝: add deprecation warnings to core lib
2023-08-29 RA: refactor🎨: sample weight transform matrix * Only for old algorithm * For new algorithm, pass customized distance_func
2023-08-31 Matlab controller working files
